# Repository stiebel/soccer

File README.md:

# Bohlebots
<h2>collection of all published and open source software and hardware from the Bohlebots.</h2>
We are a team of students at the Gymnasium Haan in Germany. We call ourselves Bohlebots
due to the support of the Bohle company at our home town Haan.

We decided to put all our robotic stuff opensource. This includes arduino files and libraries,
eagle pcb files () and eagle libraries (lbr) for all our baords.

See the README files inside the subfolders for further detail.

STILL UNDER CONSTRUCTION

We are also taking part at the development of the https://github.com/CoRoSoN-Kit/CoRoSoN-Kit.
Here is a photo of the prototypes of a mainboard and an IR-seeker-ring:

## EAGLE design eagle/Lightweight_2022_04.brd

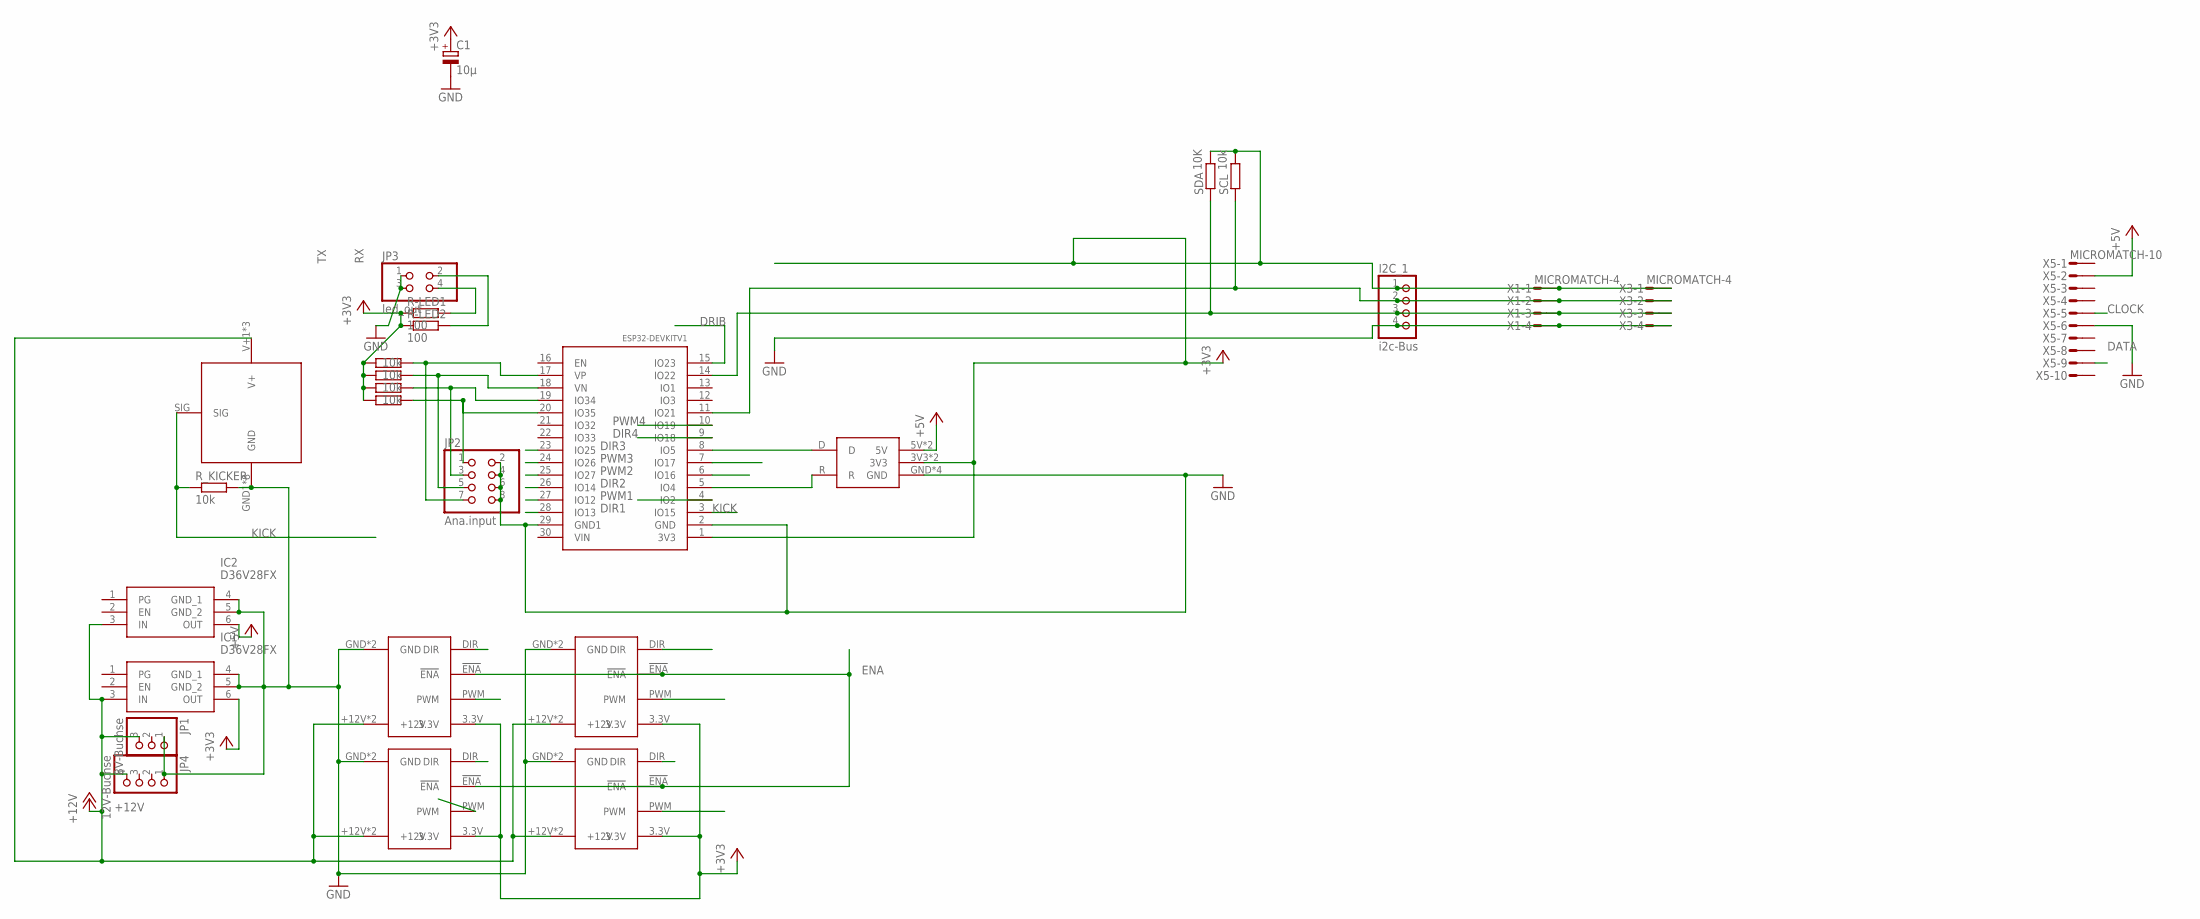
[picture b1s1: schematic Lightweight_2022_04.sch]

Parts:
C1: 10µ; E2,5-6E
I2C_1: i2c-Bus; 1X04
IC1, IC2: D36V28FX
JP1: 8V-Buchse; 1X03
JP2: Ana.input; 2X04
JP3: led_out; 2X02
JP4: 12V-Buchse; 1X04
R-LED1, R-LED2: 100; 0207/10
R_AD14, R_AD25, R_AD26, R_AD27: 10k; 0207/10
R_KICKER: 10k; 0207/10
SCL: 10k; 0207/10
SDA: 10K; 0207/10
U$5: CANBUS
U$11, U$14, U$15, U$16: IFX9201BREAKOUT
U$13: ESP32DEVKITV1; ESP32-DEVKITV1
U$17: KICKER
X1, X3: MICROMATCH-4
X5: MICROMATCH-10

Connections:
+3V3: C1.+, I2C_1.1, IC1.6 (OUT), R-LED1.1, R-LED2.1, R_AD14.1, R_AD25.1, R_AD26.1, R_AD27.1, SCL.2, SDA.2, U$5.3V3, U$5.3V3_1 (3V3), U$11.3.3V, U$13.1 (3V3), U$14.3.3V, U$15.3.3V, U$16.3.3V, X1.1, X3.1
+5V: IC2.6 (OUT), U$5.5V, U$5.5V_1 (5V), X5.2
+12V: IC1.3 (IN), IC2.3 (IN), JP1.3, JP4.4, U$11.+12V, U$11.+12V2 (+12V), U$14.+12V, U$14.+12V2 (+12V), U$15.+12V, U$15.+12V2 (+12V), U$16.+12V, U$16.+12V2 (+12V), U$17.V+1 (V+), U$17.V+2 (V+), U$17.V+3 (V+)
CLOCK: I2C_1.3, SDA.1, U$13.14 (IO22), X1.3, X3.3, X5.5
D: U$5.D, U$13.8 (IO5)
DATA: I2C_1.2, SCL.1, U$13.11 (IO21), X1.2, X3.2, X5.9
DIR1: U$13.28 (IO13), U$16.DIR
DIR2: U$13.26 (IO14), U$15.DIR
DIR3: U$11.DIR, U$13.23 (IO25)
DIR4: U$13.9 (IO18), U$14.DIR
DRIB: U$13.15 (IO23)
ENA: U$11.!ENA, U$13.4 (IO2), U$14.!ENA, U$15.!ENA, U$16.!ENA
GND: C1.-, I2C_1.4, IC1.4 (GND_1), IC1.5 (GND_2), IC2.4 (GND_1), IC2.5 (GND_2), JP1.1, JP2.2, JP2.4, JP2.6, JP2.8, JP3.1, JP3.3, JP4.1, R_KICKER.2, U$5.GND, U$5.GND_1 (GND), U$5.GND_2 (GND), U$5.GND_3 (GND), U$11.GND, U$11.GND2 (GND), U$13.2 (GND), U$13.29 (GND1), U$14.GND, U$14.GND2 (GND), U$15.GND, U$15.GND2 (GND), U$16.GND, U$16.GND2 (GND), U$17.GND1 (GND), U$17.GND2 (GND), U$17.GND3 (GND), U$17.GND4 (GND), U$17.GND5 (GND), U$17.GND6 (GND), U$17.GND7 (GND), U$17.GND8 (GND), X1.4, X3.4, X5.6
KICK: R_KICKER.1, U$13.3 (IO15), U$17.SIG
unnamed: JP2.7, R_AD25.2, U$13.17 (VP)
unnamed: JP2.5, R_AD26.2, U$13.18 (VN)
unnamed: JP2.3, R_AD27.2, U$13.19 (IO34)
unnamed: JP2.1, R_AD14.2, U$13.20 (IO35)
unnamed: JP3.4, R-LED1.2
unnamed: JP3.2, R-LED2.2
PWM1: U$13.27 (IO12), U$16.PWM
PWM2: U$13.25 (IO27), U$15.PWM
PWM3: U$11.PWM, U$13.24 (IO26)
PWM4: U$13.10 (IO19), U$14.PWM
R: U$5.R, U$13.5 (IO4)
RX: U$13.6 (IO16)
TX: U$13.7 (IO17)

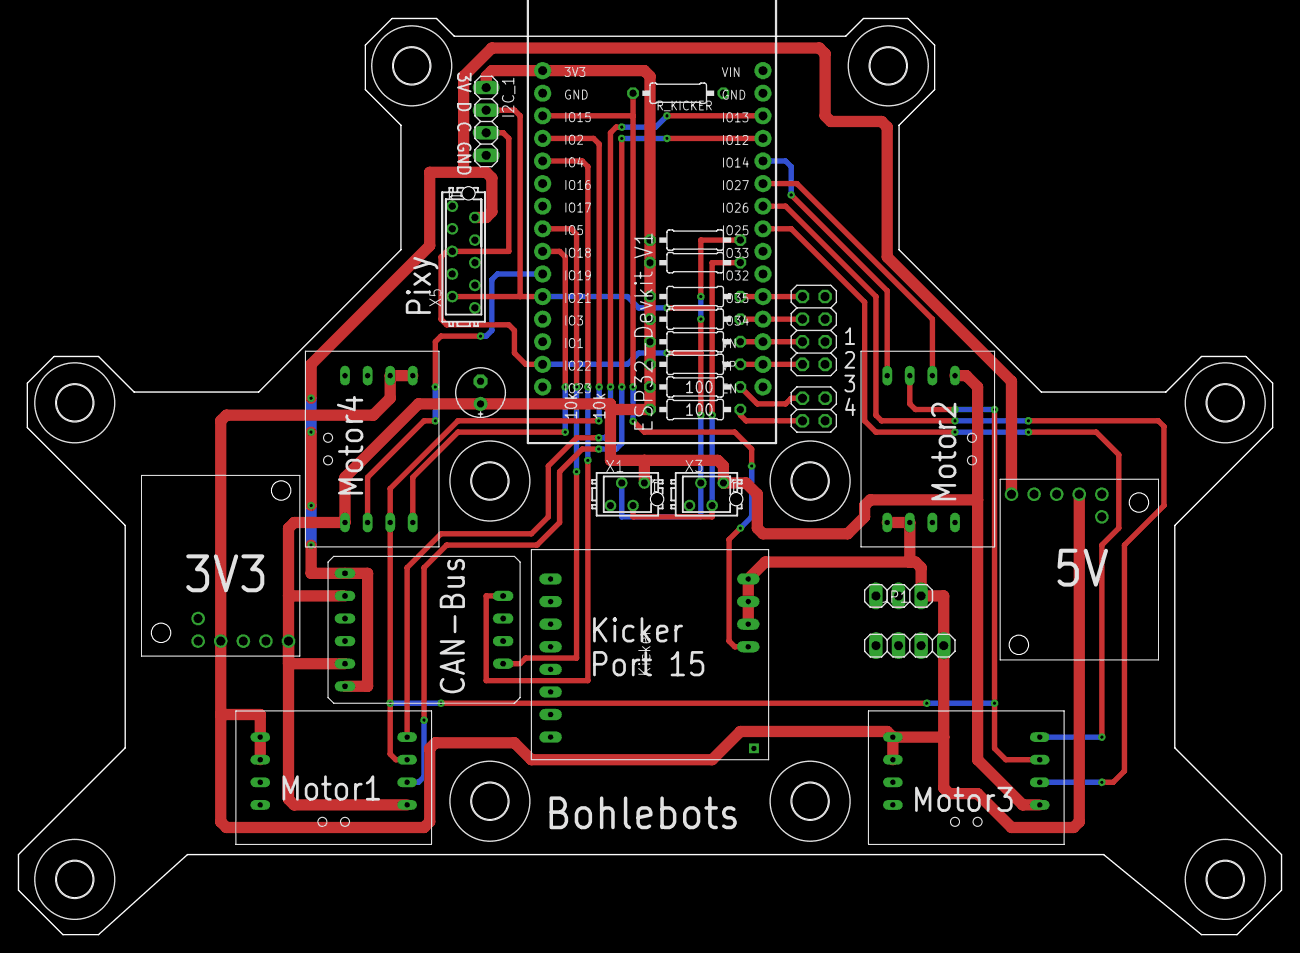
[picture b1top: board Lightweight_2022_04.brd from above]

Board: 2 copper layers, 142.0 x 103.0 mm, 37 parts (0 on the bottom side), 24 nets.

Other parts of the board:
U$1, U$2, U$3, U$4, U$6, U$7, U$8, U$9, U$10, U$12: 4,1

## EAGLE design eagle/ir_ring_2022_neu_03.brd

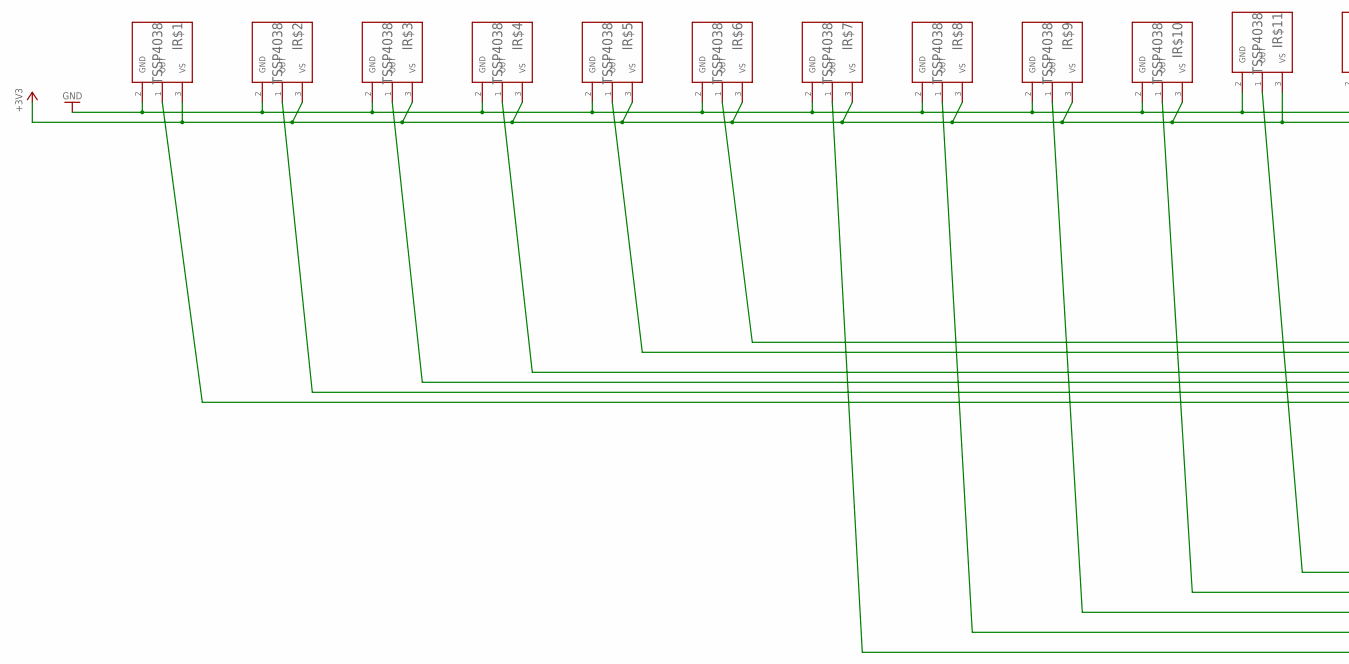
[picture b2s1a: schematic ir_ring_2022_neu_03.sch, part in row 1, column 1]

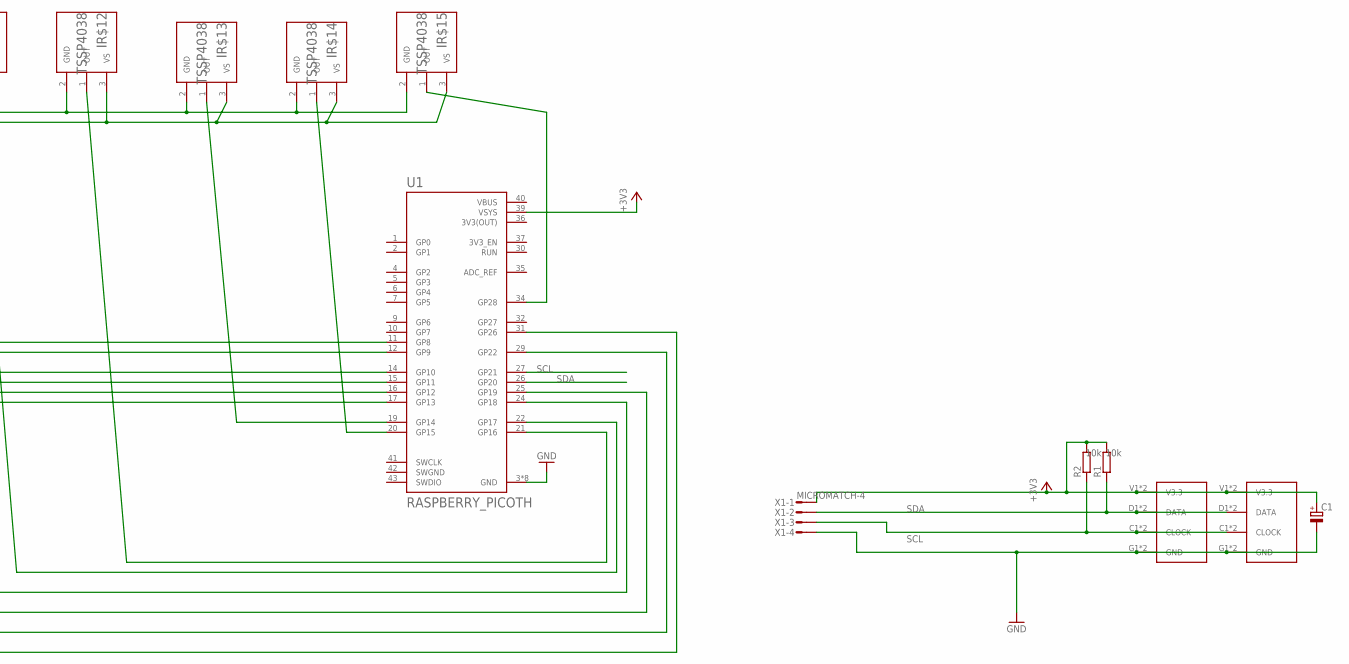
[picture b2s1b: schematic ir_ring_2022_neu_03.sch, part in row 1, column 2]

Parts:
C1: CPOL-EUE2-5; E2-5
IR$1, IR$2, IR$3, IR$4, IR$5, IR$6, IR$7, IR$8, IR$9, IR$10, IR$11, IR$12, IR$13, IR$14, IR$15: TSSP4038; XDCR_TSSP4038
R1, R2: 10k; 0204/7
U1: RASPBERRY_PICOTH; PICO-PKG-TH
U$1, U$2: TASTER_LED
X1: MICROMATCH-4

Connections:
3V3(OUT): U1.36 (3V3(OUT))
+3V3: C1.+, IR$1.3 (VS), IR$2.3 (VS), IR$3.3 (VS), IR$4.3 (VS), IR$5.3 (VS), IR$6.3 (VS), IR$7.3 (VS), IR$8.3 (VS), IR$9.3 (VS), IR$10.3 (VS), IR$11.3 (VS), IR$12.3 (VS), IR$13.3 (VS), IR$14.3 (VS), IR$15.3 (VS), R1.2, R2.2, U1.39 (VSYS), U$1.V1 (V3.3), U$1.V2 (V3.3), U$2.V1 (V3.3), U$2.V2 (V3.3), X1.1
GND: C1.-, IR$1.2 (GND), IR$2.2 (GND), IR$3.2 (GND), IR$4.2 (GND), IR$5.2 (GND), IR$6.2 (GND), IR$7.2 (GND), IR$8.2 (GND), IR$9.2 (GND), IR$10.2 (GND), IR$11.2 (GND), IR$12.2 (GND), IR$13.2 (GND), IR$14.2 (GND), IR$15.2 (GND), U1.3 (GND), U1.8 (GND), U1.13 (GND), U1.18 (GND), U1.23 (GND), U1.28 (GND), U1.33 (GND), U1.38 (GND), U$1.G1 (GND), U$1.G2 (GND), U$2.G1 (GND), U$2.G2 (GND), X1.4
unnamed: IR$1.1 (OUT), U1.17 (GP13)
unnamed: IR$2.1 (OUT), U1.16 (GP12)
unnamed: IR$3.1 (OUT), U1.15 (GP11)
unnamed: IR$4.1 (OUT), U1.14 (GP10)
unnamed: IR$5.1 (OUT), U1.12 (GP9)
unnamed: IR$6.1 (OUT), U1.11 (GP8)
unnamed: IR$7.1 (OUT), U1.31 (GP26)
unnamed: IR$8.1 (OUT), U1.29 (GP22)
unnamed: IR$9.1 (OUT), U1.25 (GP19)
unnamed: IR$10.1 (OUT), U1.24 (GP18)
unnamed: IR$11.1 (OUT), U1.22 (GP17)
unnamed: IR$12.1 (OUT), U1.21 (GP16)
unnamed: IR$14.1 (OUT), U1.20 (GP15)
unnamed: IR$13.1 (OUT), U1.19 (GP14)
unnamed: IR$15.1 (OUT), U1.34 (GP28)
SCL: R2.1, U1.27 (GP21), U$1.C1 (CLOCK), U$1.C2 (CLOCK), U$2.C1 (CLOCK), U$2.C2 (CLOCK), X1.3
SDA: R1.1, U1.26 (GP20), U$1.D1 (DATA), U$1.D2 (DATA), U$2.D1 (DATA), U$2.D2 (DATA), X1.2
SWGND: U1.42 (SWGND)
VBUS: U1.40 (VBUS)

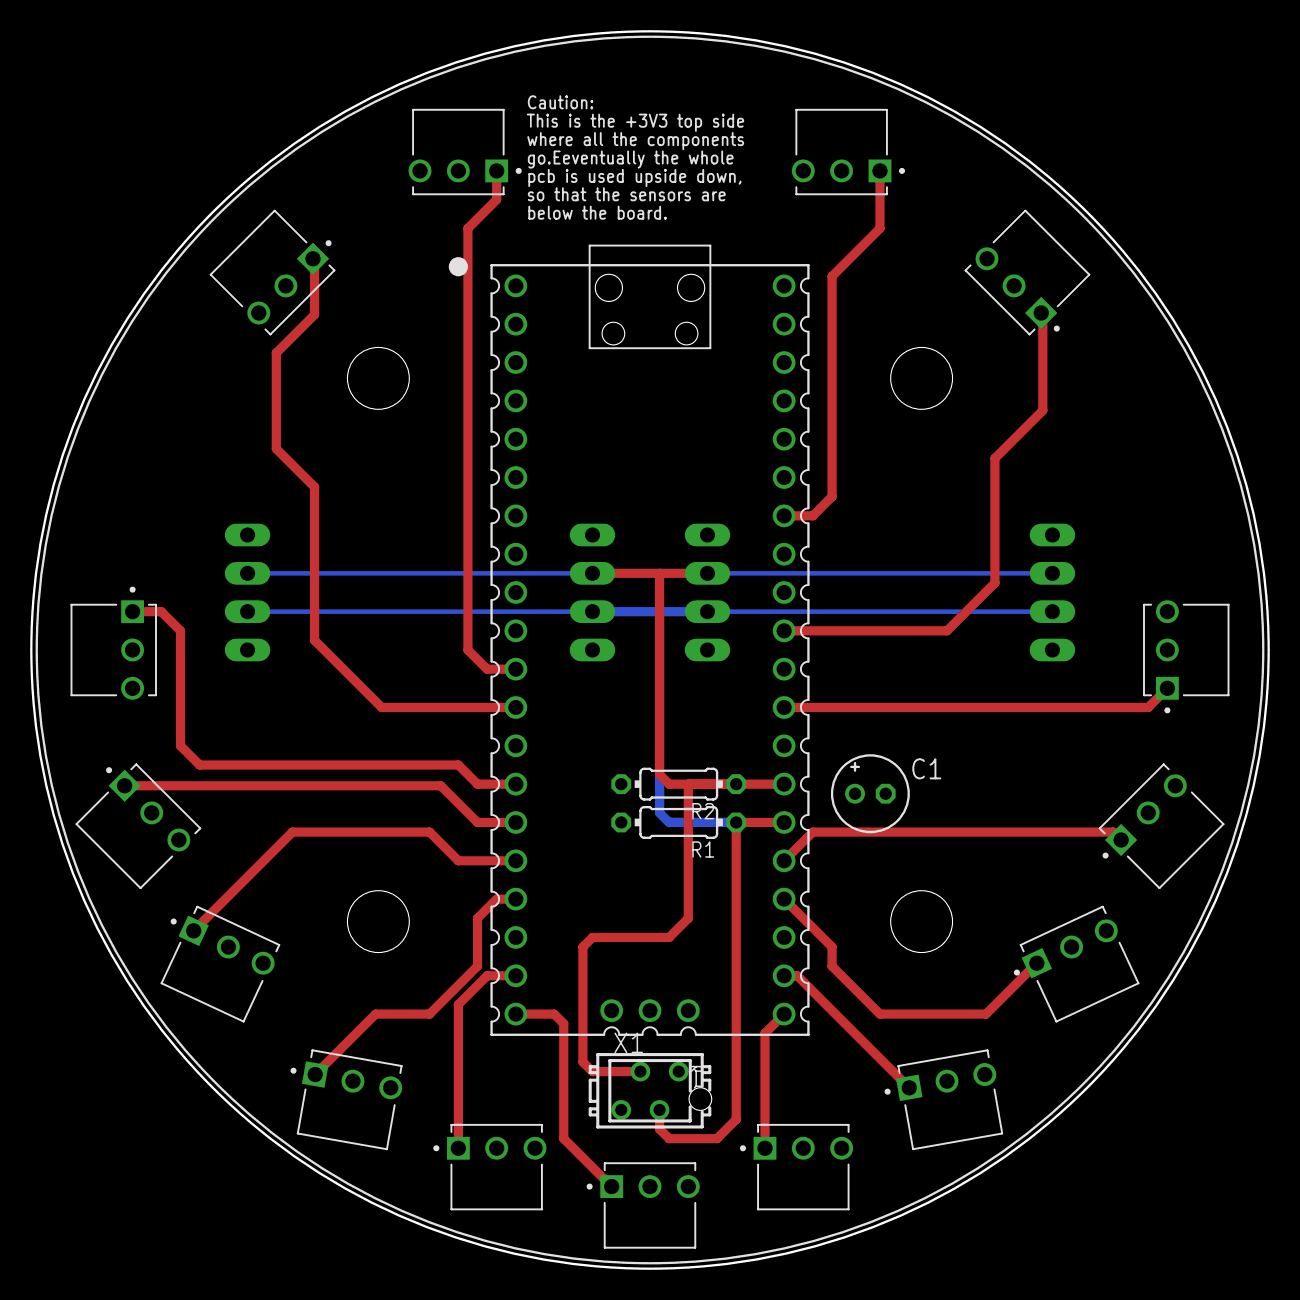
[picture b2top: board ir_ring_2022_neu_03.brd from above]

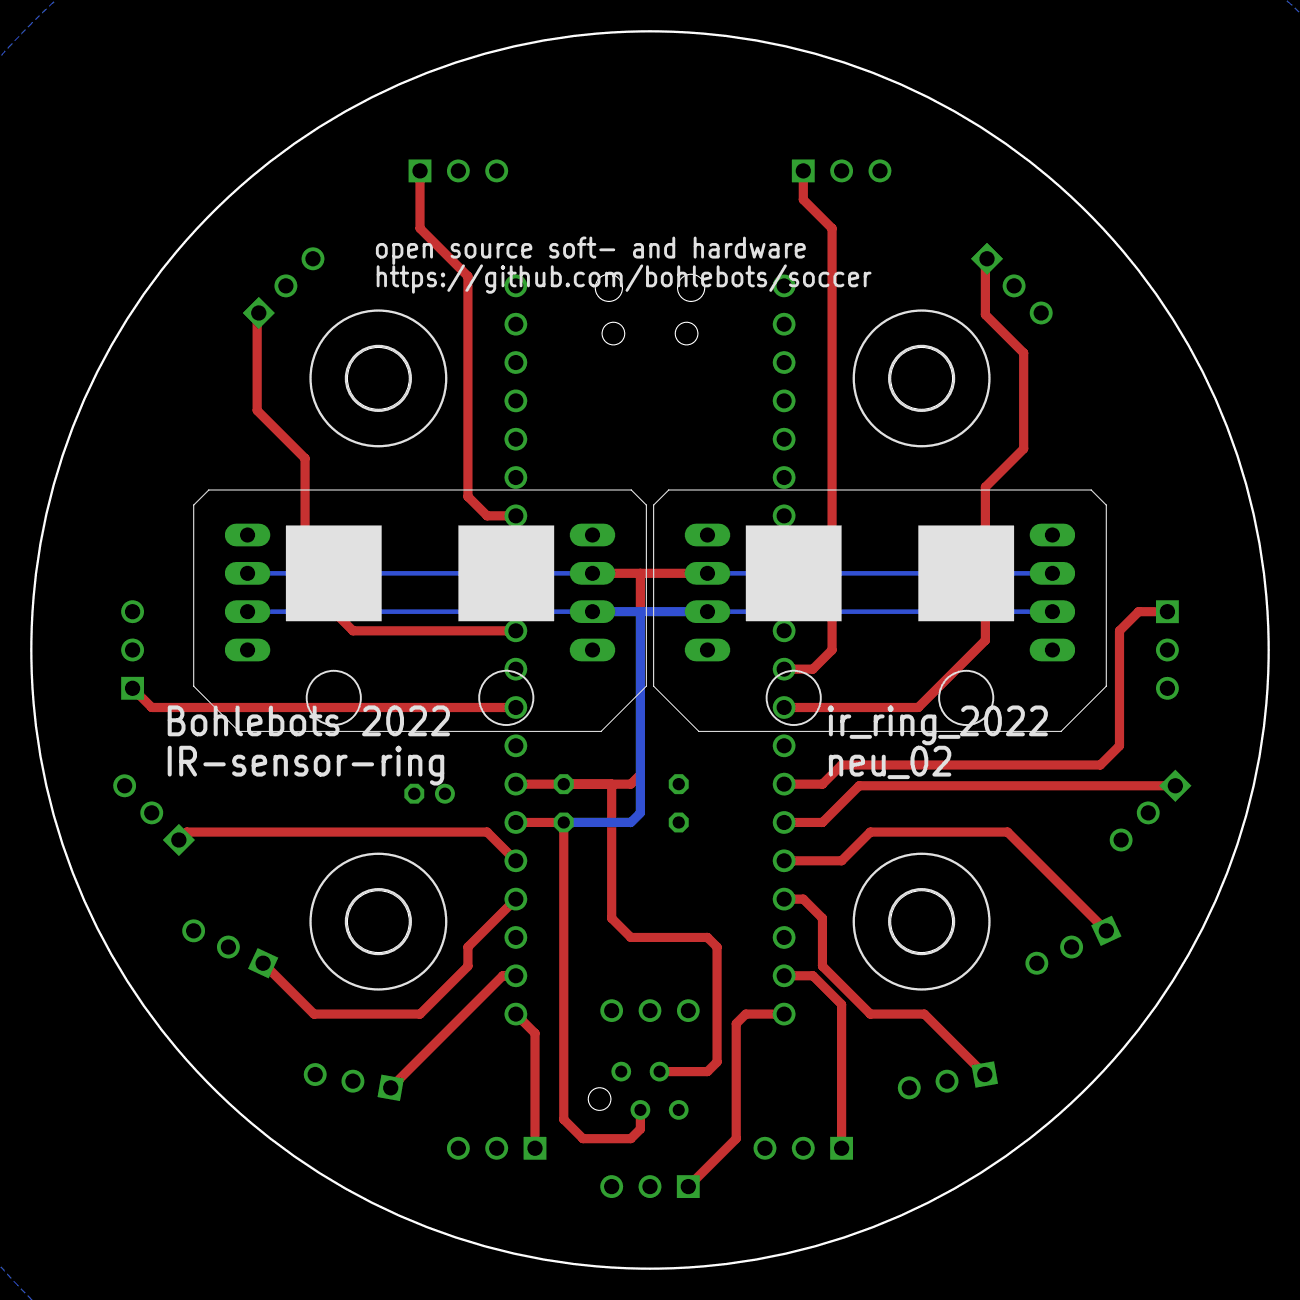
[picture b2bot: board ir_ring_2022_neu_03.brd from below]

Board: 2 copper layers, 82.0 x 82.0 mm, 26 parts (6 on the bottom side), 19 nets.

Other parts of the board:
H1, H3, H6, H8: MOUNT-HOLE4.1; 4,1

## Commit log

2026-06-28 Create Teams
    Folder wuth Special files from bohlebots Atlantis
